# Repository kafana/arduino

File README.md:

# Misc Arduino Projects

## Tools

### CrossPack for AVR Development (OS X)

https://www.obdev.at/products/crosspack/index.html

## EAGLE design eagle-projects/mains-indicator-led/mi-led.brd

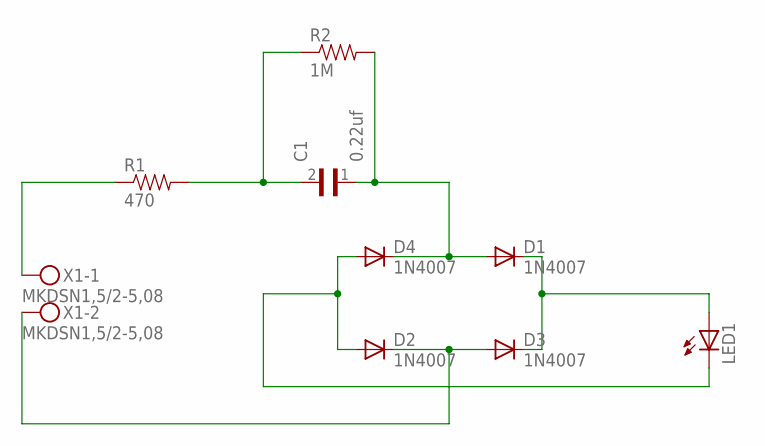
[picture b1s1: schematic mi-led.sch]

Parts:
C1: 0.22uf; WCAP-FTX2_12.5X15X14X8.5
D1, D2, D3, D4: 1N4007; DO41-10
LED1: LED5MM
R1: 470; AXIAL-0.5
R2: 1M; AXIAL-0.5
X1: MKDSN1,5/2-5,08

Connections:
unnamed: R1.P$1 (1), X1.1
unnamed: C1.2, R1.P$2 (2), R2.P$1 (1)
unnamed: D2.C, D3.A, X1.2
unnamed: D1.C, D3.C, LED1.A
unnamed: C1.1, D1.A, D4.C, R2.P$2 (2)
unnamed: D2.A, D4.A, LED1.K (C)

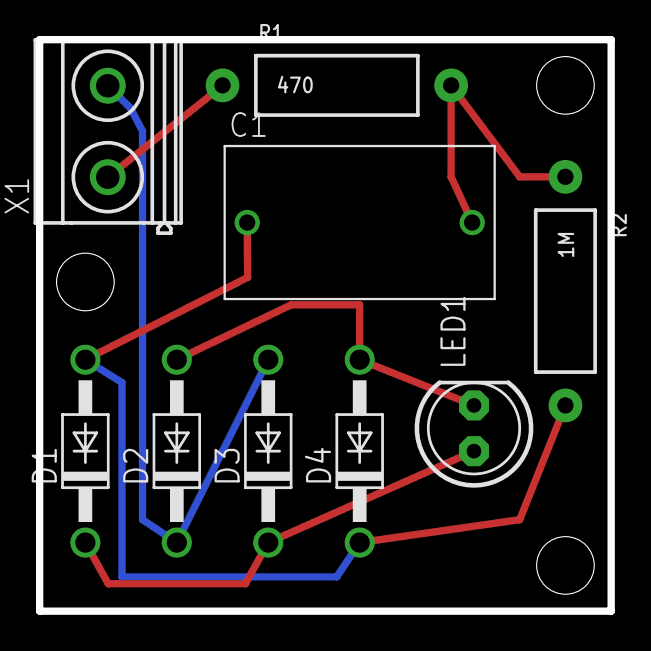
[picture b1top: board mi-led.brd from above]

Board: 2 copper layers, 31.8 x 31.8 mm, 9 parts (0 on the bottom side), 6 nets.

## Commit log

2015-12-12 Initial import of the soil monitor
2015-12-12 Fixed soil monitor sketch
2015-12-13 Added basic cozir example code
2015-12-17 Added initial display logic
2015-12-18 Misc cozir lib fixes
2015-12-22 Added atmega 2560
2016-01-07 Updated comments
2016-03-10 Added misc eagle projects
2016-03-28 Added rgb LED and LCD
2016-03-31 Completed initial tests

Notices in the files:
parts and their libraries:
Eagle_Wurth_Elektronik_Passive_Capacitor: Copyright: Würth Elektronik
SparkFun-Resistors: Licensing: Creative Commons ShareAlike 4.0 International - https://creativecommons.org/licenses/by-sa/4.0
